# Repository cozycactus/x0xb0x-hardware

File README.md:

# x0xb0x hardware: KiCad and Blender

Private working repository for the x0xb0x Eagle-to-KiCad conversion and reconstructed enclosure assembly. Original design: **Copyright (c) Limor Fried & Adafruit Industries**. x0xb0x is an Adafruit trademark.

## Open the current projects

- [Mainboard — KiCad working revision 30](kicad-working/mainboard/mainboard.kicad_pro)
- [I/O board — KiCad working revision 30](kicad-working/ioboard/ioboard.kicad_pro)
- [Schematics as PDF: mainboard](kicad-working/schematic-redraw/mainboard-schematic.pdf) and [I/O board](kicad-working/schematic-redraw/ioboard-schematic.pdf)
- [Fabrication packages — revision 30](kicad-working/fabrication/revision-30/README.md)
- [Complete assembly — Blender revision 29](kicad-working/visualization/blender-case-revision-29/x0xb0x-populated-with-case.blend)
- [KiCad notes](kicad-working/README.md) and [Blender views and limitations](kicad-working/visualization/blender-case-revision-29/README.md)

Keep each complete project folder together: symbols, footprints and STEP models use project-relative paths. The Blender file embeds the populated boards and can be opened without the original workspace or external board exports. The current scene was saved with Blender 5.2.2 LTS. The current KiCad projects were checked using KiCad 10.0.7.

See [opening and verification instructions](docs/OPENING.md) for a fresh download.

## What is included

- Both editable KiCad schematics and routed PCBs, project-local libraries and all 491 fitted component models.
- The original four Eagle files, byte-for-byte preserved under [original-eagle](original-eagle/).
- The corrected Blender enclosure, original panel DXFs, model generators, reference sources, attribution and verification reports.
- Complete PCB-mounted LED models with black STD240B spacers at all 40 positions. Their lenses pass through the front panel; the earlier duplicate lens objects were removed.
- All 23 button caps attached to their PCB switches in the exploded view, with their assembled positions retained.
- The detailed rear jacks and photo-qualified bent-back regulator/heatsink arrangement.
- Open rear socket mouths in the complete assembly: five obsolete solid display disks removed, and through-bores added to the three audio jack nuts and washers.
- The rear plate seated on the original Eagle I/O datum, with the three audio jack shoulders on its inner face.
- The I/O board on the original rear-panel height datum, with the USB shell now retaining its printed0.38mm body-to-PCB gap and the audio jacks centred in their holes.
- Solder terminals on every fitted model: the 12 models that had none now carry terminals from their manufacturer drawings, with the drawing/footprint conflicts recorded.
- A [simulation of the VCF and the whole analog section](kicad-working/validation/vcf-simulation/README.md) in ngspice, generated from the KiCad schematic and compared with published analysis of the TB-303 filter, with WAV renders from the line output. Nothing in it is measured on hardware.
- [Adapter boards](kicad-working/adapters/ssip5-dual/README.md) that replace the rare 2SC1583 and 2SC2291 dual transistors with current parts, without changing the mainboard. They are designed and checked in KiCad and in simulation; nothing has been ordered or built.
- [FR-4 main and rear panels](kicad-working/panels/README.md), drawn as KiCad boards with silkscreen legends so a PCB fab can make them. They are checked in KiCad and against part drawings; nothing has been ordered, made or fitted.
- A [parts order list](parts/README.md) for one unit: Mouser numbers, stock and prices as read, substitutes for the rare parts and fit notes checked against the footprints.

Blender views: **frame 1** assembled, **frame 80** exploded, **frame 120** control-side inspection, **frame 160** wiring study. The caps are intentionally hidden in the two inspection views.

## Validation and known limits

Blender29 brings the scene level with KiCad30 on the mainboard. The two SC-59 chips Q128 and Q139 stand at their footprints, and the do-not-place JFETs Q28 and Q39 they replace are out of the scene, so it shows the board as built and still holds 491 fitted models; Blender28 still shows the JFETs. The eight mainboard layer meshes are a fresh KiCad export in the scene's own materials. No chip model overlaps a neighbour. Q128 is the tight one, between C33 and standing resistor R105: its model is 0.35 mm from C33's and 0.42 mm from R105's, and its gate land ends 0.08 mm from R105's model in plan. See the [revision notes](kicad-working/visualization/blender-case-revision-29/README.md) and [validation](docs/blender-jfet-sites.json).

KiCad30 puts two SC-59 chips on the mainboard, Q128 and Q139, next to the rare JFETs Q28 and Q39, so that no rare transistor is left on the board. The holes stay, every original pad, track, via and drill still matches the Eagle board, and nothing has been built or measured. See [the SMD sites](kicad-working/smd-sites/README.md).

Blender28 brings the scene level with KiCad29 on the mainboard. The four chips stand at their footprints, and the do-not-place SIP pairs they replace are out of the scene, so it shows the board as built and still holds 491 fitted models; Blender27 still shows the pairs. The eight mainboard layer meshes are a fresh KiCad export in the scene's own materials, which also brings the earlier KiCad board changes into the scene. No chip model overlaps a neighbour; the closest is thermistor R100A0, 0.07 mm from Q126's top edge. See the [revision notes](kicad-working/visualization/blender-case-revision-28/README.md) and [validation](docs/blender-smd-sites.json).

KiCad29 puts four SOT-363 chips on the mainboard, next to the rare SIP pairs Q12, Q21, Q22 and Q26, so the board can be built with parts in production. The SIP holes stay, every original pad, track, via and drill still matches the Eagle board, and nothing has been built or measured. See [the SMD sites](kicad-working/smd-sites/README.md).

KiCad28 redraws both schematics by hand, block by block, on A3 sheets. Every pin is on the same net as on the board copper and in the original Eagle schematic, and the board files change only in the links from footprints to symbols, so the revision 27 fabrication packages still apply. See the [redraw notes](kicad-working/schematic-redraw/README.md).

KiCad27 makes both boards orderable. The first fabrication export, re-imported against the board files, found two defects. The mainboard's saved ground pour still cleared the SIP9 pads as they were before KiCad26 lengthened them, and touched 23 of them; KiCad26's DRC had refilled the zones before checking. The I/O board's Edge.Cuts also carried the original rear-plate datum as a second closed outline. The pours are refilled, with only their fill nodes copied in, and the four datum lines move to Dwgs.User. DRC of the copper as saved is clean, every other DRC item equals KiCad26, and the Eagle comparison is unchanged apart from the datum lines. The [order packages](kicad-working/fabrication/revision-27/README.md) (Gerbers, drills, drill maps, BOM, placement, fab notes with the owner's choices) pass a re-import against the board files and a gerbv re-export. See the [revision-27 notes](kicad-working/validation/models-review-27/README.md).

KiCad26 restores the two conversion differences KiCad25 recorded: the 27 SIP9 pads of IC14, IC15A and IC15B now have Eagle's 1.408x2.816mm size, and the 461 name labels sit at the original smashed positions, rotations and sizes, with the 11 references KiCad ends in 0 printing their Eagle names (MIXOUT, IC15A, ...). Every pad and every silkscreen text now matches the original Eagle CAM output; via tenting, the NPTH stop frame and the IC25 mask corners remain as recorded. Non-silkscreen DRC results are unchanged and silkscreen warnings decrease. See the [revision-26 notes](kicad-working/validation/models-review-26/README.md).

KiCad25 compares both boards' Gerbers and drills with the original Eagle 4.13 boards and settles the three recorded connection gaps. Drills, copper tracks, vias, pads, pour outlines and connectivity, paste and all non-text silkscreen reproduce the original, except 27 SIP9 pads that the import made 0.78mm shorter; 445 name labels sit at library positions instead of the original smashed positions. The +5V gap at S22 is closed inside switches S19 and S22, whose pins 1-2 form one strip, now declared as KiCad jumper pad groups. The two GND gaps are the original's drawn ground splits, joined without loops through the J3-J7 wiring, and stay unrouted. No copper changed. See the [fabrication comparison](kicad-working/validation/models-review-25/fabrication-comparison/README.md) and [readiness record](docs/fabrication-readiness.json).

KiCad24 and Blender27 print the part markings of the17 ICs, transcribed from the original kit photographs (part number and code lines, no logos), raised0.03mm in light-grey ink on the unchanged chip tops. See the [marking sources and validation](docs/ic-markings.json).

KiCad23 and Blender26 seat IC3 and IC2 in their original-BOM sockets (AMP390262-5 and390261-2) using TE manufacturer models: black ladder housings5.10mm tall with tin contacts, the chips resting on top. Socket tails fit the original drills; no new contact appears. See the [socket sources and validation](docs/ic-socket-completion.json).

KiCad22 and Blender25 give all212 fixed resistors the original kit's colour bands, read from the original parts page: tan5% bodies with four bands and light-blue1% bodies with five (R4, R5, R106, R74-R90). Body and lead geometry are the unchanged KiCad models, so no outline, clearance or fit changes. R16 and R106 follow the parts page; their PCB values are unchanged. See the [band sources and validation](docs/resistor-colour-bands.json).

KiCad21 and Blender24 give all39 radial electrolytics Xicon XRL bodies, the original kit's light-blue Mouser parts, sized from the XRL datasheet and checked against the original kit photographs:5x11mm for33 parts,6.3x11mm for C7/C8 and10x12.5mm for C43, replacing generic5mm- and10mm-tall cans. Leads land on the original2.54/5.08mm holes; C17 and C3/C5 keep their geometry in the photo colours. C8's larger can reaches the TM6 trimmer by about0.09mm, recorded rather than moved. See the [sources, sizes and validation](docs/electrolytic-xrl-correction.json). The expanded BOM, later printed from the wiki by the owner, confirms all seven XRL part numbers (its two100uF numbers are transposed against their descriptions, which the circuit shows are right) and208 of209 resistor values; see the [expanded BOM cross-check](docs/expanded-bom-crosscheck.json).

KiCad20 and Blender23 correct both Micro-Ohm LPTC12 PTCs from the original manufacturer page recovered by the user:3.7x1.9mm body and0.45mm leads, replacing the footprint-derived7.62x2.54mm body and assumed0.50mm leads. Original PCB spacing and all component transforms remain. See the [source dimensions and validation](docs/ptc-primary-dimension-correction.json).

Additional [terminal and source checks](docs/terminal-isolation-and-source-review.json) found no overlap or touching among151 pairs of separate solder-terminal solids across12 families at25 references. The original Mitsubishi2SC1583 datasheet is now included, with fresh package/pad checks for Q12/Q21/Q26. These checks preserve KiCad19 and Blender22 geometry.

KiCad19 and Blender22 add the40 black STD240B spacers from the user-supplied VCC drawing. Its section A-A confirms that0.240inch includes the end lands, preserving the existing6.096mm LED seat. The original three LED solids, optics and panel projection remain unchanged. See the [spacer source and validation](docs/led-spacer-completion.json).

KiCad working revision18 and Blender revision21 correct USB0 from the recovered original-BOM Kobiconn154-2442-E drawing (KC-301021,2006). The shell sits0.38mm above the PCB; signal pins project2.91mm and mounting tabs3.72mm below it. The previous mixed model used a flush body and FCI61729 terminal lengths. Four signal pins also intersected the illustrative metal floor; their exits now have shell clearances and white insulation. Four illustrative gold mating strips are added. The original footprint, model transform, body width/depth/height, mating cavity, all other components and every assembly pose are preserved. See the [USB correction](docs/usb-kobiconn-correction.json) and [source review](kicad-working/validation/models-review-18/README.md).

KiCad working revision 17 and Blender revision 20 colour the TL1100F tact-switch legs as metal. Revision 8 had coloured the publisher CAD by face position and left black the leg faces that rise above the board outside the housing. Only colours change; the geometry is byte-identical. See the [TL1100F colour report](docs/tl1100f-leg-colour.json).

KiCad working revision 16 and Blender revision 19 rebuild the two Grayhill 25L rotary switches (S3, S4) from the Series 25L drawing and a product photograph of the hex-output part. The photograph supplies the round drum top with lock lugs, the white `8 4 2 1 C` label band, and the green output board with solder joints; the drawing puts the non-turn tab on the centre line opposite the pins. Printed dimensions and pins are unchanged, and the four MT holes stay empty because the BOM part 25LB22-H has no bracket. See the [Grayhill rebuild report](docs/grayhill-25l-rebuild.json), the [KiCad review](kicad-working/validation/models-review-16/README.md) and the [revision-19 notes](kicad-working/visualization/blender-case-revision-19/README.md).

KiCad working revision 15 and Blender revision 18 join every drawing-derived terminal to its body. Checking pots in the KiCad 3D viewer showed that 24 terminals of six models (the Alpha and Panasonic pots, the CTS encoder, the NKK bracket legs, SDS-50J pins 4–5 and the MJ-3536N tip and shunt) stopped just above the seat beside the body. The drawings show them leaving the base edge and turning down; each now has a formed leg with its own section. Leg height and bend are assumptions, and pins, holes and the recorded hole conflicts are unchanged. A new check confirms that all 133 placed terminal pieces join their bodies. See the [terminal join report](docs/terminal-join-correction.json), the [KiCad review](kicad-working/validation/models-review-15/README.md) and the [revision-18 notes](kicad-working/visualization/blender-case-revision-18/README.md).

KiCad working revision 14 and Blender revision 17 correct four of those terminal models against their drawings, after an independent source review of the 19 recorded hole conflicts. The Alpha and Panasonic potentiometer tabs move to their slot centres: their drawings' 13.0 and 10.60 mm dimensions run across the outer slot edges, which revision 13 misread as centre spacing. PJ-202AH terminal 2 becomes the 2.50 mm blade, and the SDS-50J pins follow the period CUI drawing (rev D, 2006), now retained in the repository. The conflicts fall from 19 to 11. The NYS216 rows remain 0.35 mm from the footprint rows with no source explaining the Eagle datum, and the illustrative USB board locks exceed Eagle's smaller nominal mounting holes; their actual deformation and fitted variant remain unqualified; PJ-202AH terminal 3 and SDS-50J pins 1 and 2 differ by Eagle's grid positions within drawing tolerance. Only 12 model paths and 12 Blender meshes change. See the [terminal correction report](docs/terminal-drawing-correction.json), the [KiCad review](kicad-working/validation/models-review-14/README.md) and the [revision-17 notes](kicad-working/visualization/blender-case-revision-17/README.md).

KiCad working revision 13 and Blender revision 16 add solder terminals from the manufacturer drawings to the 12 component models that had none: the NYS216, SDS-50J, MJ-3536N, PJ-202AH and USB-B rear connectors, the bent-back MC78M05, the LPTC thermistors, the CTS encoder, the Alpha and Panasonic potentiometers, and the NKK and Grayhill switches (25 placed references). Every fitted component now has a lead in every drilled hole, except the four Grayhill bracket holes, whose legs the drawing does not define. Terminals follow the drawing dimensions and were not moved to the pads. A native audit against the real drills records 19 nominal interferences where a drawing and the footprint disagree, for example the NYS216 rows 0.35 mm from the footprint rows and the Alpha and Panasonic bracket tabs outside their holes; neither source was altered to fit. Previous body solids, copper, placement and every Blender pose are preserved. Terminal thicknesses, bends and some widths are labelled assumptions. See the [terminal completion report](docs/terminal-completion.json), the [KiCad review](kicad-working/validation/models-review-13/README.md) and the [revision-16 notes](kicad-working/visualization/blender-case-revision-16/README.md).

Blender revision 15 seats the I/O board on the height datum of the original rear-panel DXF, which measures every cutout from 0.250 in (6.350 mm) above the plate's lower edge. Both POWER/USB rectangles start exactly there, and the audio and DIN holes sit their part axis heights above it within 0.001 and 0.018 mm. Revision 14's 6.269 mm compromise left the POWER/USB bodies 0.081 mm below their cutouts. Only the I/O board, with its wiring-study endpoints and the three audio nuts that thread onto the jacks, now moves 0.081 mm upward. No port overlaps plate material, the audio jacks are centred in their holes and no new contacts appear. The original CV/GATE holes sit 0.21 in (5.334 mm) above that datum, against the MJ-3536N's 5.5 mm axis, which the manufacturer's revision history shows unchanged from the 2005 release through 2024. They read as an inch rounding within the part's ±0.2 mm tolerance, so the modelled bushings clear by only about 0.005 mm; see the [MJ-3536N note](kicad-working/validation/rear-seating-review/source-audit/README.md#mj-3536n-axis-height-follow-up-to-blender-revision-15). See the [rear height datum report](docs/rear-height-datum-correction.json) and the [revision-15 notes](kicad-working/visualization/blender-case-revision-15/README.md).

Blender revision 14 seats the rear plate on the datum drawn in the original Eagle I/O board. A detached Dimension-layer strip lies 0.508 mm (0.020 in) behind the PCB rear edge, exactly at the three REAN audio footprint origins, and the original finishing manual clamps the plate with those three jacks. Revision 13 had put the plate inner face on the PCB edge, so each audio shoulder ran 0.508 mm (about 102 mm³) into the plate. Only the I/O board placement moved 0.508 mm toward the case front, with its wiring-study endpoints. The audio shoulders seat within 0.001 mm, the DIN and MJ fronts sit 0.508 mm behind the plate, and a triangle-level screen finds no new contacts. KiCad, copper, placement, the case, plate cutouts and all other poses are unchanged. Reading the strip as the plate section is an interpretation, since the strip is wider than the plate. See the [rear plate datum report](docs/rear-plate-datum-correction.json) and the [revision-14 notes](kicad-working/visualization/blender-case-revision-14/README.md).

Blender revision 13 and KiCad working revision 12 correct the contact pattern of all four SDS-50J DIN models. The primary drawing's 25-degree leaders describe elongated slot tilts; our previous reconstruction used them incorrectly for the outer contact center positions. The two outer centers now lie on the horizontal diameter. The three lower contacts, nominal body envelope, all component poses, materials, case geometry and animation are preserved. See the [contact correction report](docs/din-contact-correction.json) and [model source review](kicad-working/validation/models-review-12/README.md).

The downloaded Warehouse model was placed unchanged into two separate local full-case comparison scenes. Its flange dimensions and body-to-pin datum differ from the current drawing and PCB: its terminals match the drawing's pattern measured from the back of a 0.2 mm thicker flange. At the revision-13 plate position, a nominal pin-fitting shift moved its flange 0.12 mm into the panel material. At the revision-14 plate datum the same fit clears the plate by 0.388 mm. It has not replaced the active drawing-derived model. The received CAD and comparison scenes remain outside this published repository.

Blender revision 12 corrected three rear MIDI legends against the original Eagle schematic and PCB wiring: DIN1 is MIDI OUT, DIN2 is MIDI THRU (displayed as THRU), DIN3 is MIDI IN, and DIN4 remains DIN SYNC (displayed as SYNC). In that revision only the three existing text bodies changed; their fonts, materials, style, positions and 0.01 mm panel offset are preserved. Every connector, component, PCB, enclosure, hardware mesh and animation was preserved in revision 12. See the [DIN/MIDI source review](kicad-working/validation/din-midi-review/README.md) and [correction report](docs/din-midi-correction.json). The [original receipt and source inspection](kicad-working/validation/din-midi-review/user-model-inspection.json) is preserved separately.

Blender revision 11 places the eleven existing rear legends on the plate. Their glyphs previously floated more than 1.24 mm above it and cast detached shadows; they now retain a 0.01 mm rendering gap. Their typography, ink material and in-plane positions are preserved, along with all connector, nut, washer, PCB and enclosure geometry. The text remains presentation artwork; the original rear DXF contains manufacturing annotations rather than these control legends. See the [rear seating and legend review](docs/rear-seating-and-legends.json).

The revision-11 seating review recorded nominal intersections: the three audio body shoulders extended 0.508 mm into the panel from its inner plane, and the power/USB bodies overlap the rectangular lower edges by approximately 0.081 mm. Revision 14 resolves the audio intersection from the original Eagle datum, and revision 15 resolves the power/USB lower-edge overlap from the original rear-DXF height datum. Historical body/terminal registration and fitted variants remain uncertain, and the original cutouts are unchanged. The legend correction does not establish mechanical clearance. Detailed [scene measurements](kicad-working/validation/rear-seating-review/scene-audit/README.md) and [source limits](kicad-working/validation/rear-seating-review/source-audit/README.md) remain explicit.

Blender revision 10 refines the three NYS216 mounting nuts from the retained official DXF, PDF and product photograph: 15 mm wrench flats, a circular rear flange and a rounded front treatment. Only these three presentation meshes change. The washer geometry, native connectors, all other components, case, materials, positions and animation remain as in revision 9. The source dimensions and illustrative details are separated in the [hardware refinement review](kicad-working/validation/nys216-hardware-quality/README.md). The front rounding remains a visual reconstruction; undimensioned rear-face features are omitted. See the [nut refinement report](docs/nys216-hardware-refinement.json).

Blender revision 9 corrects rear socket occlusion in the presentation geometry. The installed native connector models already had open entrances; five separate display disks and six solid audio hardware pieces covered them. The correction preserves all 491 native component assemblies, the case and panel cutouts, component positions, materials and animation. Independent checks inspect all 11 rear ports using the evaluated assembly geometry, including the DIN contact mouths and the passages around the power pin and USB tongue. See the [rear opening review](kicad-working/validation/rear-openings-review/scene-audit/README.md) and [source model review](kicad-working/validation/rear-openings-review/source-audit/README.md). Earlier preservation checks did not test these openings.

The audio nut bores use an illustrative 9.6 mm clearance around the installed 9.525 mm nose; washer bores use the retained 11.3 mm drawing dimension. The manufacturer's DXF and product photo confirm the six-flat SW15 nut, as recorded in the [hardware source review](kicad-working/validation/rear-openings-review/source-audit/NYS216-HARDWARE.md). The older 3/8-32 UNEF source and later M11 drawing describe different threads, so the exterior hardware depiction does not establish interchangeability or physical fit. Those revision-9 and revision-10 updates changed only Blender and preserved the KiCad revision-11 projects and electrical findings.

KiCad revision 11 updates 24 historical 2SC536F transistor illustrations and both ceramic resonators. Its saved model integration passed 5,200 checks and source/native integration review passed 4,041 checks; the companion Blender revision 8 passed 12,819 preservation checks. The transistor dimensions are typical values, and the historical NP package choice remains a documented inference from the BOM and original photo. Resonator maximum envelopes and complete leads are preserved. Both schematics passed ERC with zero errors and warnings under the recorded project rules. Existing PCB connection gaps remain at mainboard IC9.8/GND, mainboard S22.1/+5V and I/O MIXOUT0/GND; recorded DRC and schematic-parity warnings also remain. The 3D updates did not alter the circuit, copper routing or footprint placement.

The LED height uses the BOM's named STD240B 0.24-inch spacer. An older assembly table says 0.22 inch; the discrepancy is documented. Exact spacer molding, button retention/travel, historical vendor variations, assumed terminal sections, the remaining omitted locators, reconstructed enclosure tolerances and the wiring study remain qualified. These files do not establish physical assembly readiness.

Twelve reusable checks are included:

- `python3 scripts/verify_project.py` checks file hashes, the 375 current KiCad project files, original Eagle sources and saved Blender scene.
- `python3 scripts/verify_kicad_dependencies.py` checks that symbols, footprints and all 497 placed models, the six do-not-place parts among them, resolve inside the checkout, without global KiCad libraries. Both Python checks accept `--root PATH` and require Python 3.9 or later.
- `scripts/verify_blender_scene.py` runs inside native Blender and checks embedded components, complete LED assemblies, cap attachment across views and external file dependencies. See the opening instructions for the command, including the required failure exit-code option.
- `scripts/verify_rear_openings.py` runs inside native Blender and checks the actual rear mating passages for scene geometry that covers them. It accounts for intentional contacts and recessed inserts.
- `scripts/verify_kicad_blender_models.py` runs inside native Blender, exports both KiCad PCBs to a temporary folder with `kicad-cli`, and checks that every placed KiCad model matches the scene's embedded native mesh: footprint frame, bounds, centroid, surface area and triangle count. Footprints marked do-not-place are left out of the export, because the scene shows the boards as built. Blender-only enclosure and presentation parts are outside its scope. It needs KiCad installed; set `KICAD_CLI` to override the macOS path.
- `scripts/verify_drill_fit.py` runs inside native Blender, exports both KiCad PCBs to a temporary folder and cuts every placed model at both board faces and mid-depth against the drills read from the PCB files. It requires a lead in every drilled hole and fails on any interference or board crossing not declared, with its source reason, in [docs/drill-fit-allowances.json](docs/drill-fit-allowances.json). It exports the do-not-place SIP pairs too, so their leads stay checked against the holes that remain. Currently it measures 489 models and finds only the declared exceptions: the TL1100F free-state retention kinks, the NYS216 row offset, the USB press-fit board locks, two SDS-50J pins, PJ-202AH terminal 3 and the empty Grayhill bracket holes.
- `scripts/verify_terminal_joins.py` runs inside native Blender, exports both KiCad PCBs to a temporary folder and checks that every terminal of the drawing-derived terminal models (`*_Terminals.step`) touches or enters its body. It currently checks 133 terminal pieces at 25 references.
- `python3 kicad-working/schematic-redraw/verify_current_functions.py` replays 214 original-source and current-PCB MIDI function checks. It does not modify the project.
- `python3 kicad-working/fabrication/revision-30/verify_packages.py` re-imports the fabrication packages and checks every pad, via, track, zone fill, mask and paste opening, drill and outline segment against the board files, re-exports every file with gerbv, and runs KiCad's DRC on the copper as saved. It needs KiCad and gerbv.
- `python3 kicad-working/validation/vcf-simulation/verify_report.py` checks the stored VCF and analog-section simulation results against the published statements they are compared with, and that the simulated parts still match the schematic. It needs numpy and `kicad-cli`, and says nothing about real hardware.
- `python3 kicad-working/schematic-redraw/verify_redraw.py` regenerates the schematics and compares them with the installed files, checks their file format and sheet instances, compares every pin with the board copper and the original Eagle nets, checks each footprint's link to its symbol, and reruns ERC and DRC. `--mutation` also leaves one wire out of each sheet to show that the comparison fails. It needs `kicad-cli`.
- `python3 -I kicad-working/adapters/ssip5-dual/make_package.py --check` reruns ERC and DRC on the adapter boards, checks that every mainboard pad reaches the expected chip pin, reads the exported Gerbers and drills back, and compares them with their recorded hashes. It needs `kicad-cli`, and says nothing about a built adapter.
- `kicad-working/panels/make_package.py`, with any Python that has Pillow, reruns DRC on the FR-4 panels, exports them afresh, reads the Gerbers and drills back, compares them with the original panel drawings and the boards, and works out each part's margin at the worst fab tolerance.
- `python3 -I parts/scripts/build_table.py` rebuilds the parts list and checks every reference and quantity in it against the boards.

The initial revision-10 fresh download passed native KiCad ERC, model exports and 106 Blender portability checks; [historical fresh-download verification](docs/fresh-clone-verification.json) pins that source commit and scene hash. Current model integration and electrical evidence are recorded in [working validation](kicad-working/validation/working-validation-summary-revision-30.json). Fresh ERC on both boards reports zero errors and warnings under the recorded rules; DRC now checks the copper as saved, without a zone refill. Both boards' non-silkscreen DRC violations, parity and ignored-check lists exactly equal the previous fresh reports, and I/O silkscreen-to-edge warnings decrease with the datum outline removed; the remaining unconnected items are the two original GND splits. The saved Blender28 audit passes 16 saved-scene comparison checks against revision 27, 106 portability checks and 44 rear-opening checks using 974 rays, and all 491 placed KiCad models match the scene's native meshes. The Blender13 contact-correction, Blender14 plate-datum, Blender15 height-datum, Blender16 terminal, Blender17 terminal-correction, Blender18 terminal-join and Blender19 Grayhill evidence, including the four circuit-function checks, is retained.

These checks do not establish physical fit. The historical native audit/model-generation scripts retain source paths and may require macOS applications, earlier source baselines or other tools; their recorded results are preserved as evidence.

Key reports: [working validation](kicad-working/validation/working-validation-summary-revision-30.json), [fabrication readiness](docs/fabrication-readiness.json), [fabrication packages](kicad-working/fabrication/revision-30/README.md), [FR-4 panels](kicad-working/panels/README.md), [parts list](parts/x0xb0x-parts-order.md), [SMD sites](kicad-working/smd-sites/README.md), [VCF simulation](kicad-working/validation/vcf-simulation/README.md), [dual-transistor adapters](kicad-working/adapters/ssip5-dual/README.md), [front controls](kicad-working/validation/models-review-10/front-controls-review/final-front-control-assembly-review.md), [saved-scene verification](kicad-working/visualization/blender-case-revision-29/verification/final-saved-scene-audit.json), [Blender JFET sites](docs/blender-jfet-sites.json), [Blender SMD sites](docs/blender-smd-sites.json), [rear opening correction](docs/rear-opening-correction.json), [hardware refinement](docs/nys216-hardware-refinement.json), [rear seating and legends](docs/rear-seating-and-legends.json), [DIN/MIDI functions](docs/din-midi-correction.json), [DIN contact correction](docs/din-contact-correction.json), [rear plate datum](docs/rear-plate-datum-correction.json), [rear height datum](docs/rear-height-datum-correction.json), [terminal completion](docs/terminal-completion.json), [terminal drawing correction](docs/terminal-drawing-correction.json), [terminal joins](docs/terminal-join-correction.json), [Grayhill rebuild](docs/grayhill-25l-rebuild.json), [TL1100F leg colour](docs/tl1100f-leg-colour.json), [USB BOM correction](docs/usb-kobiconn-correction.json), [XRL electrolytics](docs/electrolytic-xrl-correction.json), [resistor colour bands](docs/resistor-colour-bands.json), [IC sockets](docs/ic-socket-completion.json), [IC markings](docs/ic-markings.json).

Delivery ZIPs, earlier experimental Blender scenes, temporary native probes, local application state and redundant board GLB exports are excluded. The revision-7 through revision-28 scenes are retained as comparison baselines for the subsequent updates. Native meshes are already embedded in the saved Blender scene. Whole-board exports can be regenerated with the recorded scripts; the last exports' hashes (revision 24; revision 25 changes no model) are recorded in `validation/models-review-24/native-export-record.json`.

## Sources and licensing

See [LICENSE.md](LICENSE.md) for asset-level attribution. Original documentation: [downloads](https://www.ladyada.net/make/x0xb0x/download.html), [parts list](https://www.ladyada.net/make/x0xb0x/fab/parts.html), [sequencer assembly](https://www.ladyada.net/wiki/x0x/sequencerfabrication). The original Eagle conversion used the existing cozycactus KiCad fork at commit `ac8691a64afa0a78d04f0073e82896bcdec82657`; no KiCad source change was required.

This repository starts with a snapshot of the current validated working files. Earlier local work is represented by the included provenance and reports, rather than an invented Git history.

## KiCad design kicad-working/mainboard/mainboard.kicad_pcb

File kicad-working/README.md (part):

# x0xb0x KiCad working revision 30

Revision30 puts two SC-59 chips on the mainboard, Q128 and Q139, next to the rare JFETs Q28 and Q39, which are now marked do-not-place. The holes stay. Every original pad, track, via and drill still matches the Eagle board. Nothing has been built or measured. Blender revision 29 has the chips and leaves those JFETs out. See `smd-sites/README.md`.

Revision29 puts four SOT-363 chips on the mainboard, Q112, Q121, Q122 and Q126, next to the rare SIP pairs Q12, Q21, Q22 and Q26, which are now marked do-not-place. The holes stay. Every original pad, track, via and drill still matches the Eagle board. Nothing has been built or measured. Blender revision 28 has the chips and leaves those pairs out. See `smd-sites/README.md`.

Revision28 redraws both schematics by hand as sets of A3 sheets, one per block: nine for the mainboard and three for the I/O board. Every pin is on the same net as on the board copper and in the original Eagle schematic, with the same names. The board files change only in the `path` lines that link footprints to symbols; copper, nets, placement, models and Gerbers are unchanged. See `schematic-redraw/README.md`.

Revision27 refills the two mainboard F.Cu ground pours, whose saved fill still cleared the SIP9 pads as they were before revision 26 lengthened them and touched 23 of them, and moves the four I/O rear-plate datum lines from Edge.Cuts, where they formed a second board outline, to Dwgs.User. Only the pours' filled polygons and the four lines' layer change; DRC now checks the copper as saved. Order packages for both boards are in `fabrication/revision-27/`. See `validation/models-review-27/`.

Revision26 gives the 27 SIP9 pads of IC14, IC15A and IC15B Eagle's restrung and elongated 1.408x2.816mm size, and places the reference labels of the 461 parts with an Eagle smashed name record at that record's position, rotation, size and layer. The 11 references KiCad ends with 0 keep their reference, hidden, and print the Eagle name through a footprint text. Drills, tracks, vias, nets, zones, placement, models and schematics are unchanged. See `validation/models-review-26/`.

Revision25 compares both boards' Gerbers and drills with the original Eagle 4.13 boards and declares the internal 1-2/3-4 strips of the 23 B3F-40XX switches as KiCad jumper pad groups. Through S19 and S22 those strips close the recorded S22 +5V gap; the two remaining GND gaps are the original's drawn ground splits, joined through the J3-J7 wiring. Copper, pads, drills, nets, zones, placement, models and the I/O project are unchanged. See `validation/models-review-25/`.

Revision24 prints the part markings of the17 ICs, transcribed from the kit photographs, on the unchanged chip models. Revision23 seats IC3 and IC2 in their original-BOM TE DIP sockets (manufacturer models) with the KiCad chips resting on top. Revision22 gives all212 fixed resistors the original kit's colour bands from the parts page (tan5%, light-blue1%) on the unchanged KiCad DIN0207 bodies; footprint caches and PCB values are unchanged. Revision21 gives all39 radial electrolytics Xicon XRL bodies from the XRL datasheet and the original kit photographs (5x11, 6.3x11 and10x12.5mm cans) with leads on the original2.54/5.08mm holes; C17 and C3/C5 are recoloured only. Revision20 corrects both PTCs from the recovered Micro-Ohm LPTC12 family page to3.7x1.9mm bodies and0.45mm leads. Original PCB spacing and model transforms remain. Revision19 adds40 VCC STD240B black spacers beneath the unchanged LED bodies and leads, from the detailed manufacturer drawing. The6.096mm seat and all existing LED transforms remain unchanged. Revision18 corrects USB0 to the recovered original-BOM Kobiconn154-2442-E drawing: body0.38mm above PCB, signal projection2.91mm, board-lock projection3.72mm, insulated signal exits and illustrative gold mating strips. Revision17's TL1100F metal leg colours are preserved. Revision 16 rebuilt the Grayhill 25L rotary switches (S3, S4) from their drawing and a product photograph. Revision 15 gave 24 terminals of six models formed legs, so every drawing-derived terminal joins its body (15 references). Revision 14 corrected four terminal models against their drawings (12 references). Revision 13 added terminals to the 12 component models that had none: 25 placed references across both boards. Revision 12's corrected SDS-50J contact pattern and revision 11's historical transistor and resonator illustrations are preserved. Both editable projects retain all 491 fitted visual models. Electrical connectivity, copper routing, footprint placement, drills, model transforms, symbol libraries and project rules are unchanged.

- Schematic PDFs: `schematic-redraw/mainboard-schematic.pdf`, `schematic-redraw/ioboard-schematic.pdf`
- Mainboard: `mainboard/mainboard.kicad_pro`
- I/O: `ioboard/ioboard.kicad_pro`
- Current complete assembly: `visualization/blender-case-revision-29/x0xb0x-populated-with-case.blend`
- Current model plan: `validation/models-review-24/combined-model-plan.json`
- SIP9 pads and name labels: `validation/models-review-26/`
- Fabrication packages (order-ready): `fabrication/revision-30/`
- Adapters for the rare dual transistors at Q12, Q21, Q22 and Q26: `adapters/ssip5-dual/` (not yet built)
- FR-4 main and rear panels: `panels/` (not yet made)
- Pour refill and I/O outline: `validation/models-review-27/`
- Fabrication comparison and connection gaps: `validation/models-review-25/`
- Source and model review: `validation/models-review-24/` (IC markings), `validation/models-review-23/` (IC sockets), `validation/models-review-22/` (resistor bands), `validation/models-review-21/` (XRL electrolytics), `validation/models-review-20/` (PTC dimensions), `validation/models-review-18/` (USB drawing correction), `validation/models-review-17/` (TL1100F colours), `validation/models-review-16/` (Grayhill rebuild), `validation/models-review-15/` (formed legs), `validation/models-review-14/` (corrections) and `validation/models-review-13/` (terminals)
- Current validation: `validation/working-validation-summary.json`

## USB BOM drawing correction

The user recovered Mouser KC-301021 (2006-07-19) for the original BOM connector. The previous illustration mixed Kobiconn body dimensions with FCI terminal lengths. The new model retains its printed outer dimensions and original XY axes while correcting the vertical dimensions. Four signal-pin solids previously intersected the metal shell floor; clearances and insulating exits now separate them. Their stock, exit skirts, mounting-fork shape and gold mating-strip dimensions remain illustrative. Original PCB pads, drills, copper, placement and model transforms are unchanged; only the USB0 model and its cache path change. See `validation/models-review-18/`.

## TL1100F leg colours

The publisher's TL1100F CAD is one grey solid. Revision 8 coloured its faces by position and left the leg faces that rise above the board, outside the 12 × 12 mm housing, black. Those 24 faces per switch now use the terminal colour; the B-rep is byte-identical, and KiCad's own export confirms the colours on all 23 switches. Only 23 PCB model paths and one footprint-cache path change.

## Grayhill 25L rebuild

A photograph of the 25L hex-output part showed a round drum top over the square base, two lock lugs, a white `8 4 2 1 C` label band, and a green output board with soldered pins. The drawing's front view puts the non-turn tab on the centre line opposite the pins. The body is rebuilt with those features, keeping every printed dimension and the pins. The four MT holes stay empty: they serve the optional 25J5155 bracket, and the BOM part 25LB22-H has no `-Z` bracket suffix. Only two PCB model paths and one footprint-cache path change. Fresh ERC is clean, and both DRC reports equal revision 15.

## Terminals joined to their bodies

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
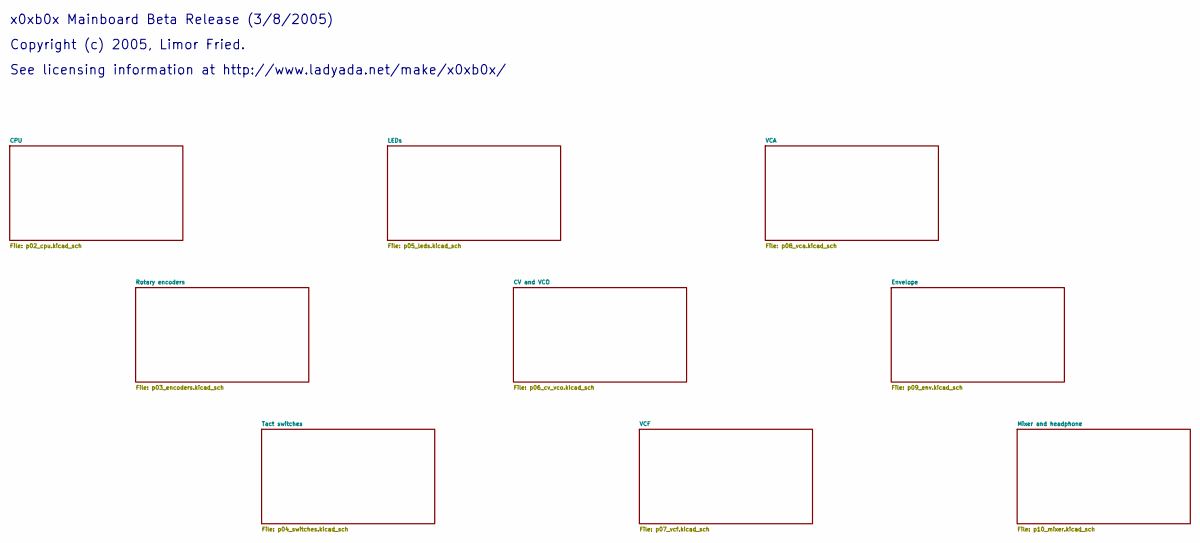
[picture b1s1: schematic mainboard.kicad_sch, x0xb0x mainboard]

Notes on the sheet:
x0xb0x Mainboard Beta Release (3/8/2005)
Copyright (c) 2005, Limor Fried.
See licensing information at http://www.ladyada.net/make/x0xb0x/

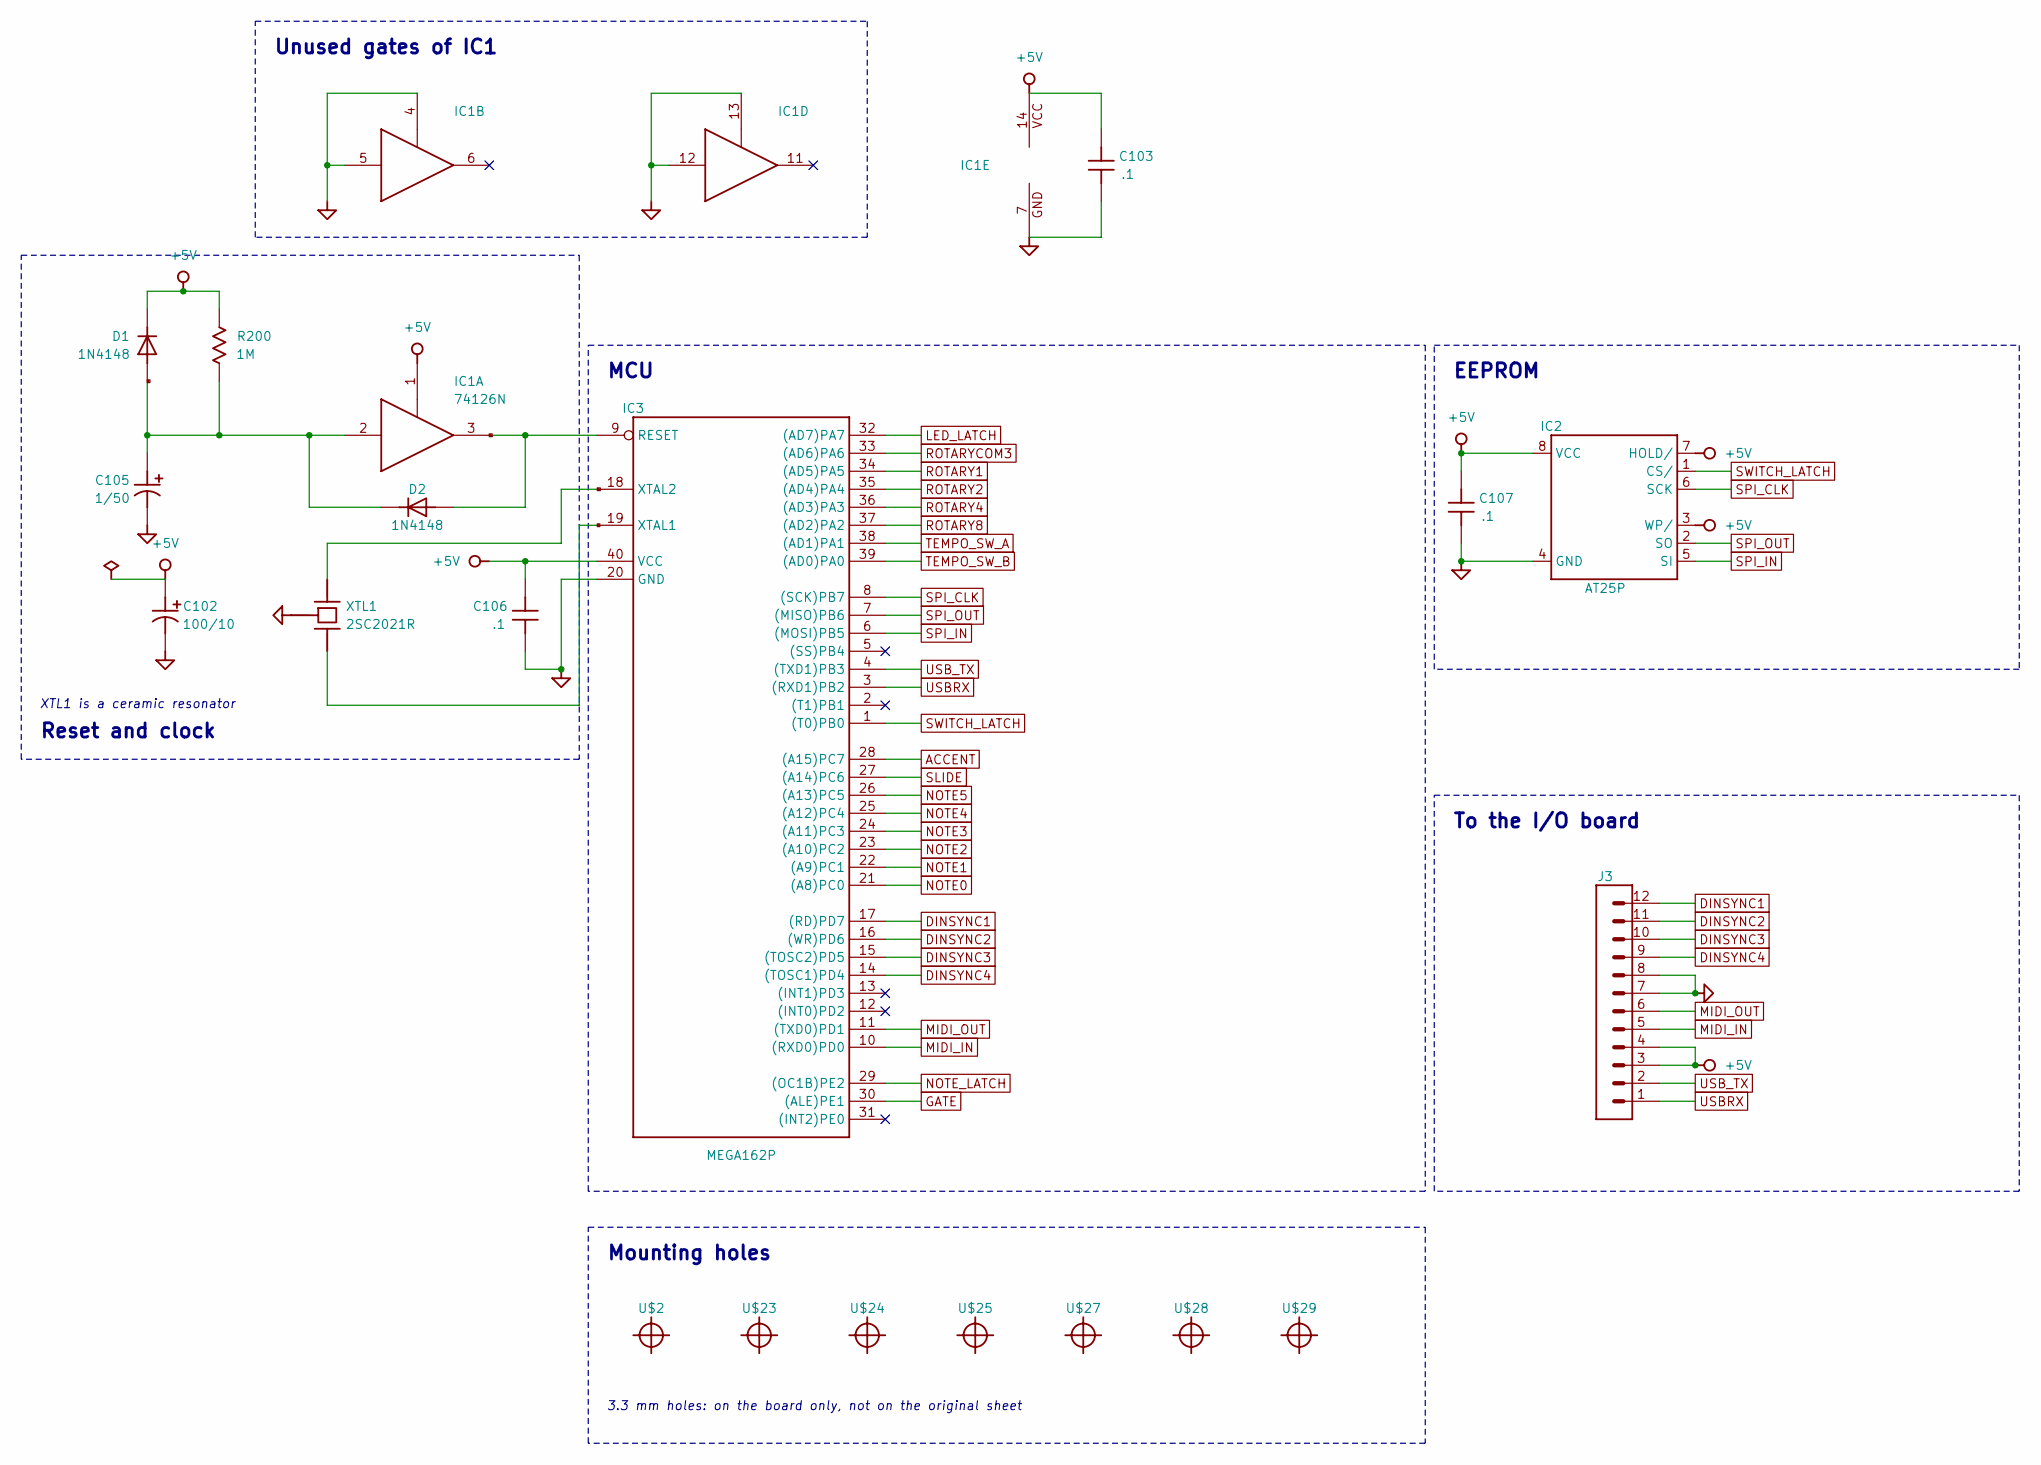
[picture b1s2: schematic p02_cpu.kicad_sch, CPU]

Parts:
C102: 100/10; E5-6
C103, C106, C107: .1; C050H075X075
C105: 1/50; E5-6
D1, D2: 1N4148; DO35-10
IC1: 74126N; DIL14
IC2: AT25P; DIL08_AT25
IC3: MEGA162P; DIL40
J3: MA12-''; MA12-1
R200: 1M; 0207_5V
U$2, U$23, U$24, U$25, U$27, U$28, U$29: 1,3
XTL1: 2SC2021R; 2SC2021

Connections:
+5V: C102.+, C103.1, C106.2, C107.2, D1.C, IC1.1 (OE), IC1.14 (VCC), IC2.3 (WP/), IC2.7 (HOLD/), IC2.8 (VCC), IC3.40 (VCC), J3.3, J3.4, R200.1; also elsewhere on the board
ACCENT: IC3.28 ((A15)PC7); also elsewhere on the board
DINSYNC1: IC3.17 ((RD)PD7), J3.12
DINSYNC2: IC3.16 ((WR)PD6), J3.11
DINSYNC3: IC3.15 ((TOSC2)PD5), J3.10
DINSYNC4: IC3.14 ((TOSC1)PD4), J3.9
GATE: IC3.30 ((ALE)PE1); also elsewhere on the board
GND: C102.-, C103.2, C105.-, C106.1, C107.1, IC1.4 (OE), IC1.5 (I), IC1.7 (GND), IC1.12 (I), IC1.13 (OE), IC2.4 (GND), IC3.20 (GND), J3.7, J3.8, XTL1.2 (C); also elsewhere on the board
LED_LATCH: IC3.32 ((AD7)PA7); also elsewhere on the board
MIDI_IN: IC3.10 ((RXD0)PD0), J3.5
MIDI_OUT: IC3.11 ((TXD0)PD1), J3.6
unnamed: C105.+, D1.A, D2.C, IC1.2 (I), R200.2
unnamed: D2.A, IC1.3 (O), IC3.9 (RESET)
unnamed: IC3.18 (XTAL2), XTL1.3 (B)
NOTE0: IC3.21 ((A8)PC0); also elsewhere on the board
NOTE1: IC3.22 ((A9)PC1); also elsewhere on the board
NOTE2: IC3.23 ((A10)PC2); also elsewhere on the board
NOTE3: IC3.24 ((A11)PC3); also elsewhere on the board
NOTE4: IC3.25 ((A12)PC4); also elsewhere on the board
NOTE5: IC3.26 ((A13)PC5); also elsewhere on the board
NOTE_LATCH: IC3.29 ((OC1B)PE2); also elsewhere on the board
ROTARY1: IC3.34 ((AD5)PA5); also elsewhere on the board
ROTARY2: IC3.35 ((AD4)PA4); also elsewhere on the board
ROTARY4: IC3.36 ((AD3)PA3); also elsewhere on the board
ROTARY8: IC3.37 ((AD2)PA2); also elsewhere on the board
ROTARYCOM3: IC3.33 ((AD6)PA6); also elsewhere on the board
SLIDE: IC3.27 ((A14)PC6); also elsewhere on the board
SPI_CLK: IC2.6 (SCK), IC3.8 ((SCK)PB7); also elsewhere on the board
SPI_IN: IC2.5 (SI), IC3.6 ((MOSI)PB5); also elsewhere on the board
SPI_OUT: IC2.2 (SO), IC3.7 ((MISO)PB6); also elsewhere on the board
SWITCH_LATCH: IC2.1 (CS/), IC3.1 ((T0)PB0); also elsewhere on the board
TEMPO_SW_A: IC3.38 ((AD1)PA1); also elsewhere on the board
TEMPO_SW_B: IC3.39 ((AD0)PA0); also elsewhere on the board
USBRX: IC3.3 ((RXD1)PB2), J3.1
USB_TX: IC3.4 ((TXD1)PB3), J3.2
XTL1: IC3.19 (XTAL1), XTL1.1 (E)

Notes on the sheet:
Reset and clock
MCU
Unused gates of IC1
EEPROM
To the I/O board
XTL1 is a ceramic resonator
Mounting holes
3.3 mm holes: on the board only, not on the original sheet

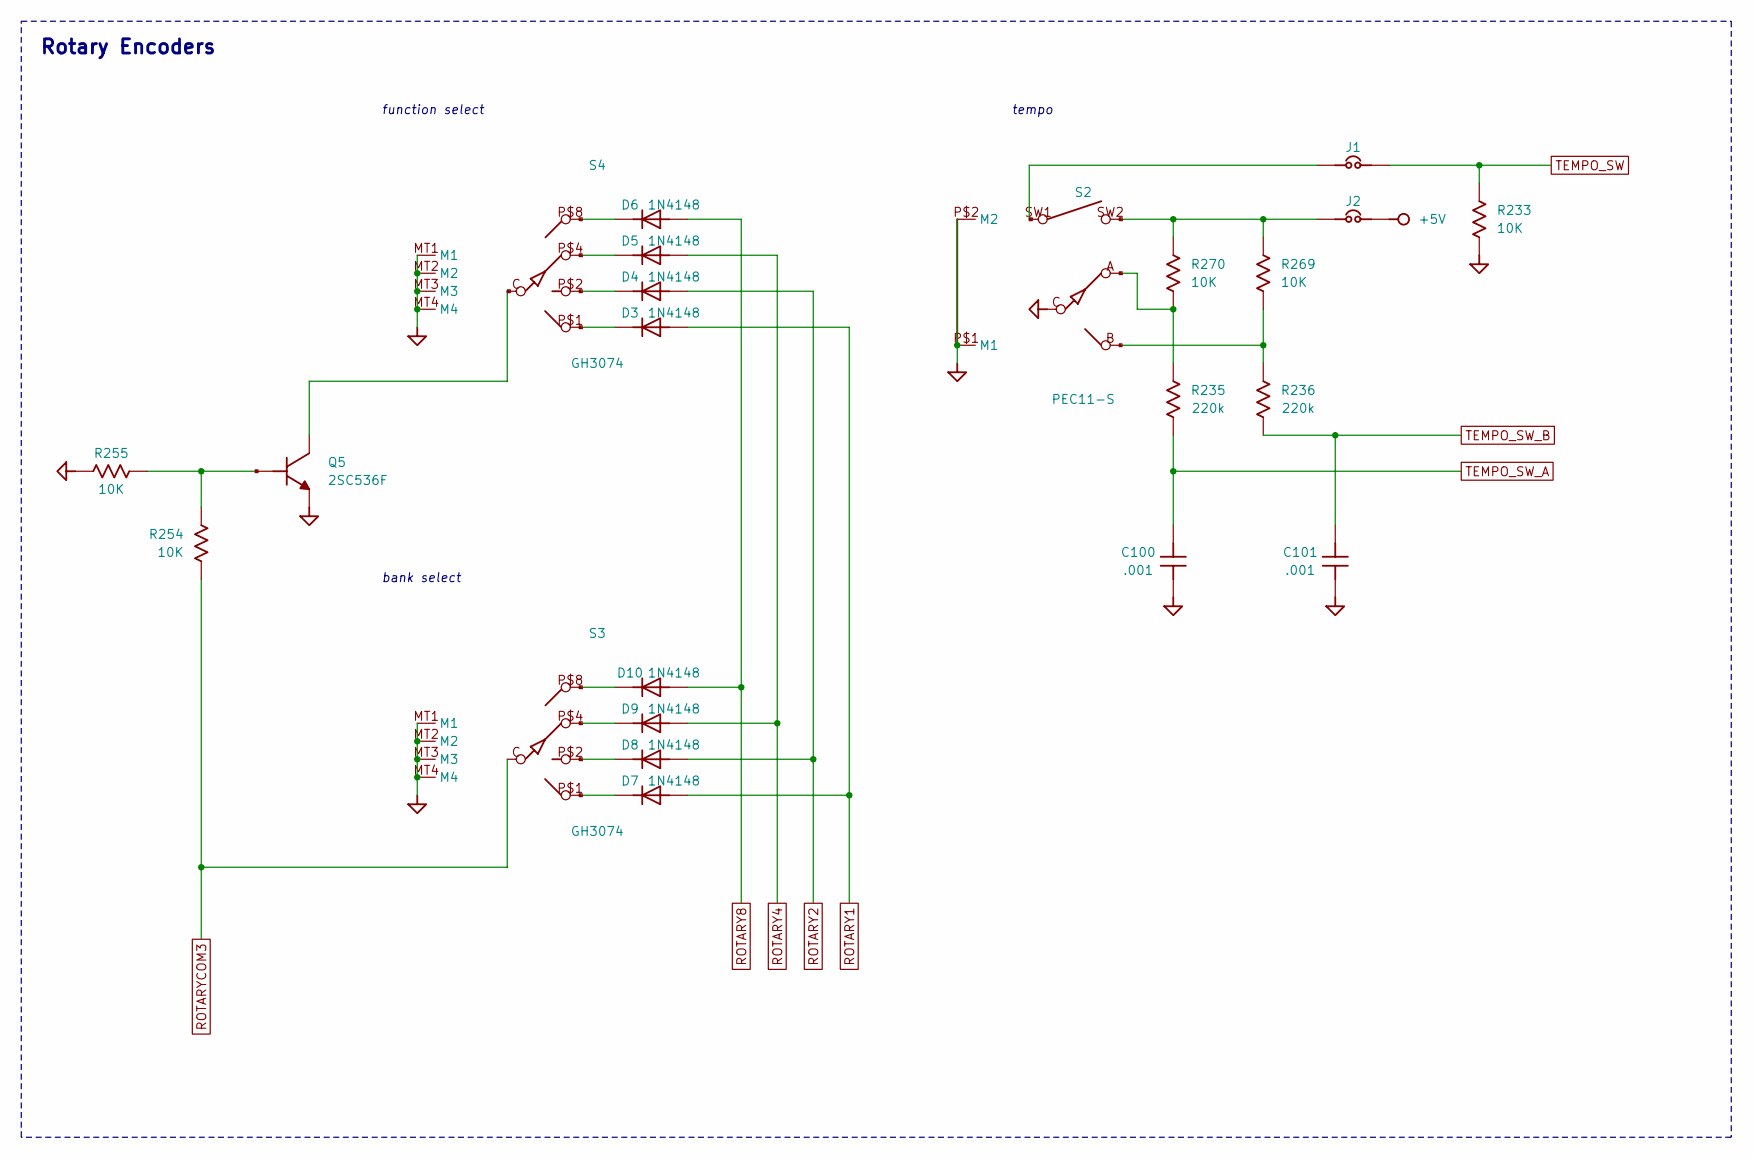
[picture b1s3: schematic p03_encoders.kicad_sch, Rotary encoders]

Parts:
C100, C101: .001; C050-035X075
D3, D4, D5, D6, D7, D8, D9, D10: 1N4148; DO35-10
J1: J12MM; 12
J2: J15MM; 15
Q5: 2SC536F
R233, R254, R255, R269, R270: 10K; 0207_5V
R235, R236: 220k; 0207_5V
S2: PEC11-S
S3, S4: GH3074

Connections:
+5V: J2.2; also elsewhere on the board
GND: C100.1, C101.1, Q5.3 (E), R233.2, R255.1, S2.C, S2.P$1 (M1), S2.P$2 (M2), S3.MT1 (M1), S3.MT2 (M2), S3.MT3 (M3), S3.MT4 (M4), S4.MT1 (M1), S4.MT2 (M2), S4.MT3 (M3), S4.MT4 (M4); also elsewhere on the board
unnamed: Q5.1 (B), R254.1, R255.2
unnamed: R236.1, R269.2, S2.B
unnamed: D3.C, S4.P$1 (1)
unnamed: D4.C, S4.P$2 (2)
unnamed: R235.1, R270.1, S2.A
unnamed: Q5.2 (C), S4.C
unnamed: D5.C, S4.P$4 (4)
unnamed: D6.C, S4.P$8 (8)
unnamed: D7.C, S3.P$1 (1)
unnamed: D8.C, S3.P$2 (2)
unnamed: D9.C, S3.P$4 (4)
unnamed: D10.C, S3.P$8 (8)
unnamed: J1.1, S2.SW1
unnamed: J2.1, R269.1, R270.2, S2.SW2
ROTARY1: D3.A, D7.A; also elsewhere on the board
ROTARY2: D4.A, D8.A; also elsewhere on the board
ROTARY4: D5.A, D9.A; also elsewhere on the board
ROTARY8: D6.A, D10.A; also elsewhere on the board
ROTARYCOM3: R254.2, S3.C; also elsewhere on the board
TEMPO_SW: J1.2, R233.1; also elsewhere on the board
TEMPO_SW_A: C100.2, R235.2; also elsewhere on the board
TEMPO_SW_B: C101.2, R236.2; also elsewhere on the board

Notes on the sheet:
Rotary Encoders
function select
bank select
tempo

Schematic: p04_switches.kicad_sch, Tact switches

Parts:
C112, C113: .1; C050H075X075
IC1: 74126N; DIL14
IC16, IC17, IC18: 74HC165N; DIL16
R201, R202, R206, R207, R209, R210, R212, R214, R216, R218, R219, R220, R224, R225, R226, R230, R231, R240, R247, R257, R259, R263: 10K; 0207_5V
R232: 10K; 0207_10
S5, S6, S7, S8, S9, S10, S11, S12, S13, S14, S15, S16, S17, S18, S19, S20, S21, S22, S23, S24, S25, S26, S27: 40-XX''; B3F-40XX

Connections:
+5V: C112.2, C113.2, IC16.16 (VCC), IC17.16 (VCC), IC18.16 (VCC), S5.2 (S1), S6.3, S7.1 (S), S8.1 (S), S9.1 (S), S10.1 (S), S11.1 (S), S12.4 (P1), S13.4 (P1), S14.2 (S1), S15.4 (P1), S16.4 (P1), S17.2 (S1), S18.2 (S1), S19.1 (S), S19.2 (S1), S20.2 (S1), S21.2 (S1), S22.1 (S), S22.2 (S1), S23.1 (S), S23.2 (S1), S24.2 (S1), S25.4 (P1), S26.4 (P1), S27.2 (S1); also elsewhere on the board
GND: C112.1, C113.1, IC16.8 (GND), IC16.10 (SER), IC16.15 (INH), IC17.8 (GND), IC17.15 (INH), IC18.8 (GND), IC18.15 (INH), R201.2, R202.2, R206.2, R207.1, R209.2, R210.2, R212.2, R214.2, R216.2, R218.2, R219.2, R220.2, R224.2, R225.2, R226.2, R230.2, R231.2, R232.2, R240.2, R247.2, R257.2, R259.2, R263.2; also elsewhere on the board
unnamed: IC1.9 (I), IC18.9 (QH)
unnamed: IC17.5 (G), R207.2, S12.1 (S)
unnamed: R257.1, S10.4 (P1)
unnamed: IC17.14 (D), R218.1, S9.3
unnamed: IC17.13 (C), S8.3
unnamed: IC17.12 (B), R225.1, S7.3
unnamed: R259.1, S11.4 (P1)
unnamed: IC18.14 (D), R230.1, S5.4 (P1)
unnamed: IC18.12 (B), R232.1, S15.1 (S)
unnamed: R206.1, S26.2 (S1)
unnamed: IC16.5 (G), S27.3
unnamed: IC17.9 (QH), IC18.10 (SER)
unnamed: IC18.4 (F), R224.1, S18.4 (P1)
unnamed: IC17.4 (F), S11.3
unnamed: R209.1, S25.2 (S1)
unnamed: IC16.9 (QH), IC17.10 (SER)
unnamed: IC16.13 (C), R214.1, S22.4 (P1)
unnamed: R210.1, S24.4 (P1)
unnamed: IC16.11 (A), S23.3
unnamed: IC16.4 (F), S26.1 (S)
unnamed: IC18.6 (H), R219.1, S20.4 (P1)
unnamed: IC16.12 (B), R216.1, S21.4 (P1)
unnamed: R240.1, S6.2 (S1)
unnamed: IC16.14 (D), S24.3
unnamed: R201.1, S27.4 (P1)
unnamed: R212.1, S23.4 (P1)
unnamed: IC18.5 (G), R220.1, S19.4 (P1)
unnamed: R231.1, S16.2 (S1)
unnamed: IC16.6 (H), R202.1, S14.3
unnamed: R263.1, S13.2 (S1)
unnamed: IC17.6 (H), S13.1 (S)
unnamed: IC18.3 (E), R226.1, S17.4 (P1)
unnamed: IC17.3 (E), S10.3
unnamed: IC17.11 (A), S6.1 (S)
unnamed: IC18.11 (A), S16.1 (S)
unnamed: IC16.3 (E), S25.1 (S)
unnamed: R247.1, S8.4 (P1)
SPI_CLK: IC16.2 (CLK), IC17.2 (CLK), IC18.2 (CLK); also elsewhere on the board
SPI_OUT: IC1.8 (O); also elsewhere on the board
SWITCH_LATCH: IC1.10 (OE), IC16.1 (SH/LD\), IC17.1 (SH/LD\), IC18.1 (SH/LD\); also elsewhere on the board
TEMPO_SW: IC18.13 (C); also elsewhere on the board

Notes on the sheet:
Tact Switches

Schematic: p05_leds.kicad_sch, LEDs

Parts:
C104, C108, C109, C110, C111: .1; C050H075X075
IC4, IC5, IC6, IC7, IC8: 74HC595N; DIL16
LED1, LED2, LED3, LED4, LED5, LED6, LED7, LED8, LED9, LED10, LED11, LED12, LED13, LED14, LED15, LED16, LED17, LED18, LED19, LED20, LED21, LED22, LED23, LED24, LED25, LED26, LED27, LED28, LED29, LED30, LED31, LED32, LED33, LED34, LED35, LED36, LED37, LED38, LED39, LED40: LED5MM
R203, R204, R205, R208, R211, R213, R215, R217, R221, R222, R223, R227, R228, R229, R237, R238, R239, R241, R242, R243, R244, R245, R246, R248, R249, R250, R251, R252, R253, R256, R258, R260, R261, R262, R264, R265, R266, R267, R268: 10K; 0207_5V
R234: 10K; 0207_15

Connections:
+5V: C104.2, C108.2, C109.2, C110.2, C111.2, IC4.10 (SCL), IC4.16 (VCC), IC5.10 (SCL), IC5.16 (VCC), IC6.10 (SCL), IC6.16 (VCC), IC7.10 (SCL), IC7.16 (VCC), IC8.10 (SCL), IC8.16 (VCC); also elsewhere on the board
GND: C104.1, C108.1, C109.1, C110.1, C111.1, IC4.8 (GND), IC4.13 (G), IC5.8 (GND), IC5.13 (G), IC6.8 (GND), IC6.13 (G), IC7.8 (GND), IC7.13 (G), IC8.8 (GND), IC8.13 (G), LED1.K (C), LED2.K (C), LED3.K (C), LED4.K (C), LED5.K (C), LED6.K (C), LED7.K (C), LED8.K (C), LED9.K (C), LED10.K (C), LED11.K (C), LED12.K (C), LED13.K (C), LED14.K (C), LED15.K (C), LED16.K (C), LED17.K (C), LED18.K (C), LED19.K (C), LED20.K (C), LED21.K (C), LED22.K (C), LED23.K (C), LED24.K (C), LED25.K (C), LED26.K (C), LED27.K (C), LED28.K (C), LED29.K (C), LED30.K (C), LED31.K (C), LED32.K (C), LED33.K (C), LED34.K (C), LED35.K (C), LED36.K (C), LED37.K (C), LED38.K (C), LED39.K (C), LED40.K (C); also elsewhere on the board
LED_LATCH: IC4.12 (RCK), IC5.12 (RCK), IC6.12 (RCK), IC7.12 (RCK), IC8.12 (RCK); also elsewhere on the board
unnamed: IC7.1 (QB), R252.2
unnamed: IC4.7 (QH), R241.1
unnamed: IC4.6 (QG), R237.1
unnamed: LED6.A, R244.1
unnamed: LED7.A, R250.1
unnamed: IC4.5 (QF), R234.1
unnamed: IC5.9 (QH*), IC7.14 (SER)
unnamed: IC5.6 (QG), R243.2
unnamed: IC5.7 (QH), R244.2
unnamed: IC5.5 (QF), R242.1
unnamed: IC7.15 (QA), R250.2
unnamed: IC7.2 (QC), R251.1
unnamed: LED1.A, R234.2
unnamed: LED2.A, R237.2
unnamed: IC7.3 (QD), R253.1
unnamed: IC7.4 (QE), R256.1
unnamed: LED14.A, R262.1
unnamed: IC8.3 (QD), R264.1
unnamed: IC8.6 (QG), R267.1
unnamed: IC8.7 (QH), R268.1
unnamed: IC8.5 (QF), R266.2
unnamed: IC5.1 (QB), R223.1
unnamed: IC8.4 (QE), R265.1
unnamed: IC5.2 (QC), R222.2
unnamed: IC5.15 (QA), R221.1
unnamed: IC5.4 (QE), R246.1
unnamed: IC5.3 (QD), R245.2
unnamed: IC4.3 (QD), R238.2
unnamed: IC4.4 (QE), R239.2
unnamed: IC4.1 (QB), R229.1
unnamed: IC7.6 (QG), R261.1
unnamed: IC7.7 (QH), R262.2
unnamed: IC7.5 (QF), R260.1
unnamed: IC4.2 (QC), R228.2
unnamed: IC4.15 (QA), R227.1
unnamed: IC8.15 (QA), R203.1
unnamed: IC8.1 (QB), R205.1
unnamed: IC8.2 (QC), R204.2
unnamed: IC6.15 (QA), R208.1
unnamed: IC6.1 (QB), R211.1
unnamed: IC6.2 (QC), R213.1
unnamed: IC6.3 (QD), R215.1
unnamed: IC6.4 (QE), R217.2
unnamed: IC6.7 (QH), R248.1
unnamed: IC6.6 (QG), R249.2
unnamed: IC6.5 (QF), R258.1
unnamed: LED9.A, R252.1
unnamed: LED10.A, R253.2
unnamed: LED11.A, R256.2
unnamed: LED12.A, R260.2
unnamed: LED16.A, R267.2
unnamed: LED3.A, R241.2
unnamed: LED4.A, R242.2
unnamed: LED5.A, R243.1
unnamed: LED15.A, R266.1
unnamed: LED8.A, R251.2
unnamed: LED13.A, R261.2
unnamed: IC4.9 (QH*), IC5.14 (SER)
unnamed: IC6.14 (SER), IC7.9 (QH*)
unnamed: IC6.9 (QH*), IC8.14 (SER)
unnamed: LED17.A, R268.2
unnamed: LED18.A, R238.1
unnamed: LED19.A, R239.1
unnamed: LED20.A, R245.1
unnamed: LED21.A, R246.2
unnamed: LED22.A, R248.2
unnamed: LED23.A, R249.1
unnamed: LED24.A, R258.2
unnamed: LED25.A, R265.2
unnamed: LED26.A, R264.2
unnamed: LED27.A, R203.2
unnamed: LED28.A, R229.2
unnamed: LED29.A, R228.1
unnamed: LED30.A, R227.2
unnamed: LED31.A, R223.2
unnamed: LED32.A, R222.1
unnamed: LED33.A, R221.2
unnamed: LED34.A, R217.1
unnamed: LED35.A, R215.2
unnamed: LED36.A, R213.2
unnamed: LED37.A, R211.2
unnamed: LED38.A, R208.2
unnamed: LED39.A, R205.2
unnamed: LED40.A, R204.1
SPI_CLK: IC4.11 (SCK), IC5.11 (SCK), IC6.11 (SCK), IC7.11 (SCK), IC8.11 (SCK); also elsewhere on the board
SPI_IN: IC4.14 (SER); also elsewhere on the board

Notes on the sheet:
LEDs

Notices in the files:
kicad-working/schematic-redraw/ioboard_sheets.py:
SPDX-License-Identifier: CC0-1.0
